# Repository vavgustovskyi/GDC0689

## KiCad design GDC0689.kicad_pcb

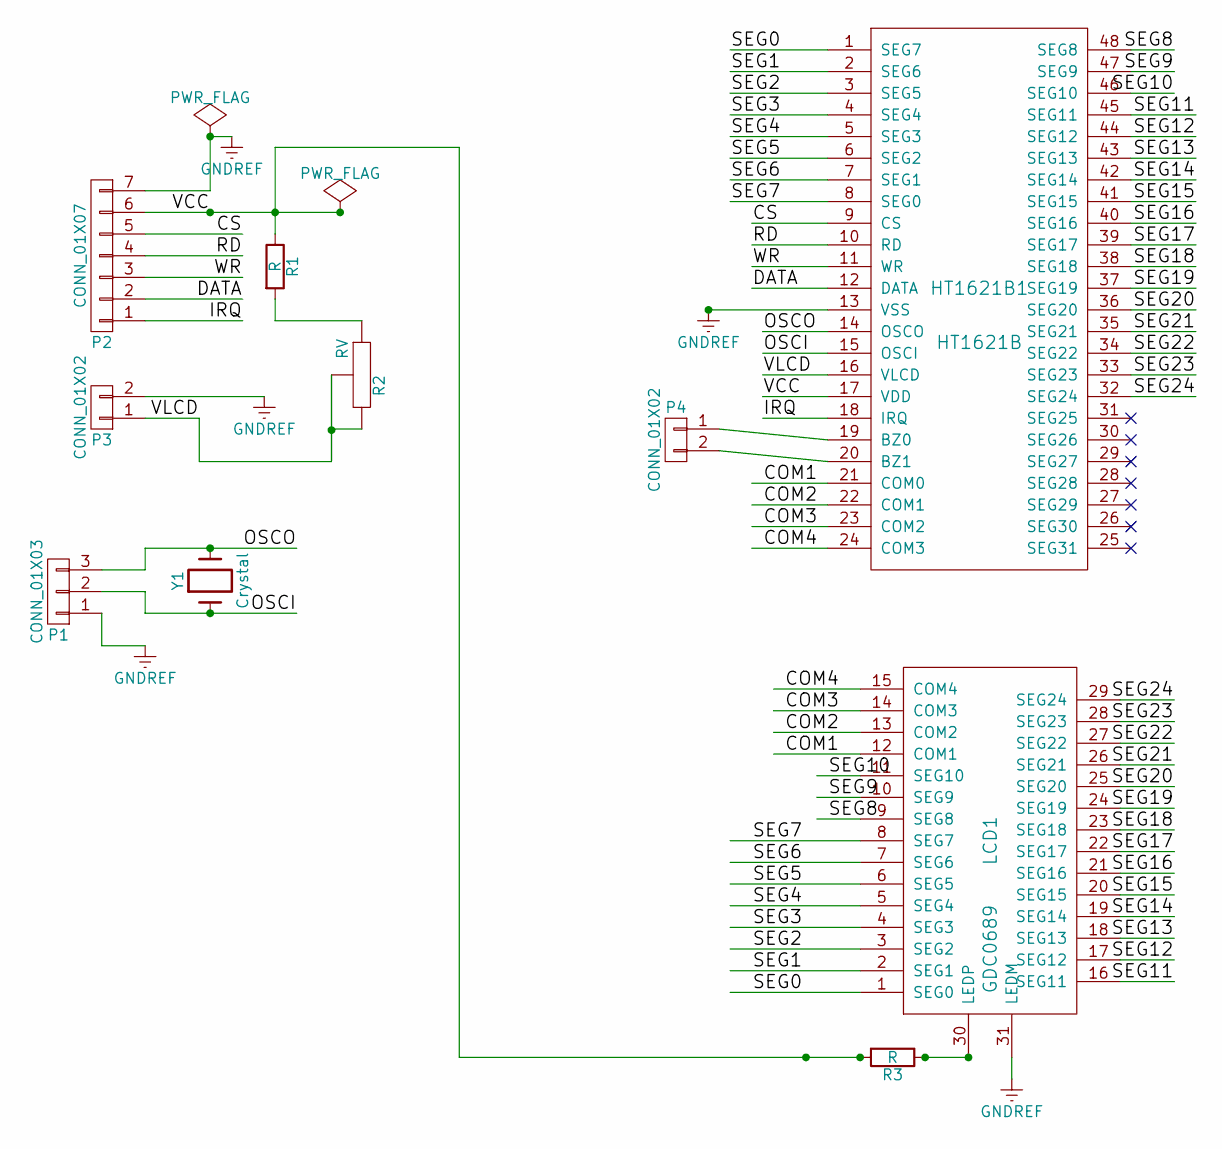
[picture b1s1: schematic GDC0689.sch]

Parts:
HT1621B1: HT1621B; SSOP-48_7.5x15.9mm_Pitch0.635mm
LCD1: GDC0689; LCD_0689
P1: CONN_01X03; Pin_Header_Straight_1x03_Pitch2.54mm
P2: CONN_01X07; Pin_Header_Straight_1x07_Pitch2.54mm
P3, P4: CONN_01X02; Pin_Header_Straight_1x02_Pitch2.54mm
R1, R3: R; R_0603
R2: RV; BOURNS-3296W
Y1: Crystal; Crystal_d3.0mm_l10.0mm_Horizontal_SMD

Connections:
/COM1: HT1621B1.21 (COM0), LCD1.12 (COM1)
/COM2: HT1621B1.22 (COM1), LCD1.13 (COM2)
/COM3: HT1621B1.23 (COM2), LCD1.14 (COM3)
/COM4: HT1621B1.24 (COM3), LCD1.15 (COM4)
/CS: HT1621B1.9 (CS), P2.5
/DATA: HT1621B1.12 (DATA), P2.2
/IRQ: HT1621B1.18 (IRQ), P2.1
/OSCI: HT1621B1.15 (OSCI), P1.2, Y1.1
/OSCO: HT1621B1.14 (OSCO), P1.3, Y1.2
/RD: HT1621B1.10 (RD), P2.4
/SEG0: HT1621B1.1 (SEG7), LCD1.1 (SEG0)
/SEG1: HT1621B1.2 (SEG6), LCD1.2 (SEG1)
/SEG2: HT1621B1.3 (SEG5), LCD1.3 (SEG2)
/SEG3: HT1621B1.4 (SEG4), LCD1.4 (SEG3)
/SEG4: HT1621B1.5 (SEG3), LCD1.5 (SEG4)
/SEG5: HT1621B1.6 (SEG2), LCD1.6 (SEG5)
/SEG6: HT1621B1.7 (SEG1), LCD1.7 (SEG6)
/SEG7: HT1621B1.8 (SEG0), LCD1.8 (SEG7)
/SEG8: HT1621B1.48 (SEG8), LCD1.9 (SEG8)
/SEG9: HT1621B1.47 (SEG9), LCD1.10 (SEG9)
/SEG10: HT1621B1.46 (SEG10), LCD1.11 (SEG10)
/SEG11: HT1621B1.45 (SEG11), LCD1.16 (SEG11)
/SEG12: HT1621B1.44 (SEG12), LCD1.17 (SEG12)
/SEG13: HT1621B1.43 (SEG13), LCD1.18 (SEG13)
/SEG14: HT1621B1.42 (SEG14), LCD1.19 (SEG14)
/SEG15: HT1621B1.41 (SEG15), LCD1.20 (SEG15)
/SEG16: HT1621B1.40 (SEG16), LCD1.21 (SEG16)
/SEG17: HT1621B1.39 (SEG17), LCD1.22 (SEG17)
/SEG18: HT1621B1.38 (SEG18), LCD1.23 (SEG18)
/SEG19: HT1621B1.37 (SEG19), LCD1.24 (SEG19)
/SEG20: HT1621B1.36 (SEG20), LCD1.25 (SEG20)
/SEG21: HT1621B1.35 (SEG21), LCD1.26 (SEG21)
/SEG22: HT1621B1.34 (SEG22), LCD1.27 (SEG22)
/SEG23: HT1621B1.33 (SEG23), LCD1.28 (SEG23)
/SEG24: HT1621B1.32 (SEG24), LCD1.29 (SEG24)
/VCC: HT1621B1.17 (VDD), P2.6, R1.1, R3.2
/VLCD: HT1621B1.16 (VLCD), P3.1, R2.2, R2.3
/WR: HT1621B1.11 (WR), P2.3
GNDREF: HT1621B1.13 (VSS), LCD1.31 (LEDM), P1.1, P2.7, P3.2
unnamed: HT1621B1.19 (BZ0), P4.1
unnamed: HT1621B1.20 (BZ1), P4.2
unnamed: LCD1.30 (LEDP), R3.1
unnamed: R1.2, R2.1

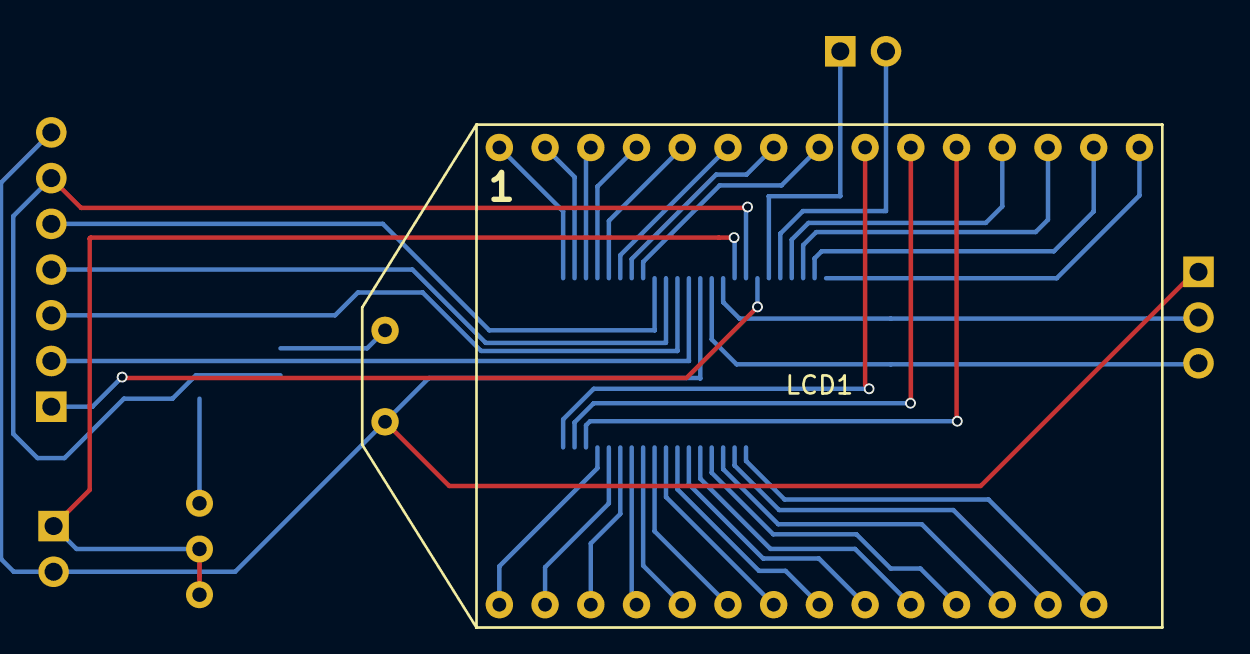
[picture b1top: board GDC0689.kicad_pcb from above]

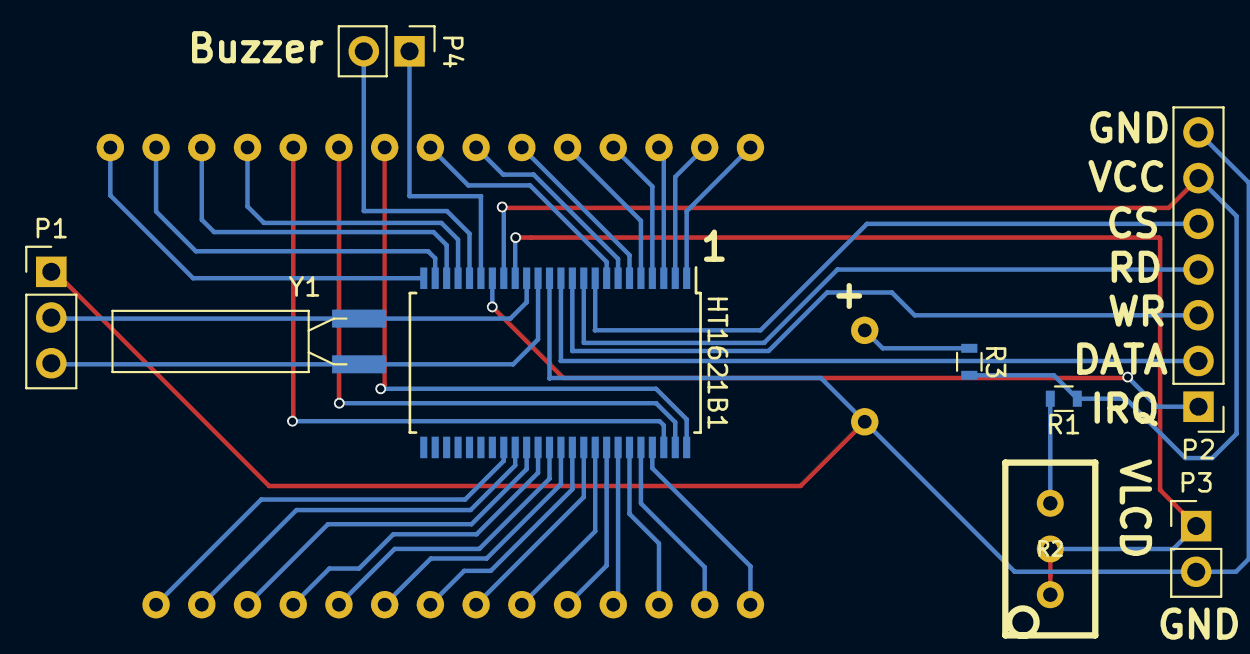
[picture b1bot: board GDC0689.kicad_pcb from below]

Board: 2 copper layers, 10 parts (9 on the bottom side), 43 nets.

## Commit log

2017-03-13 Add project
2017-03-14 Fix label
2017-03-15 Add link
